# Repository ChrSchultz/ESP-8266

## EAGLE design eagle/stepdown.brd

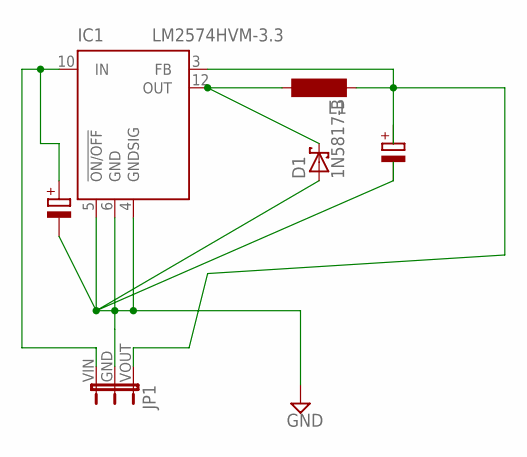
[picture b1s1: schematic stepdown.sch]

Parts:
D1: 1N5817-B; DO41-7.6
IC1: LM2574HVM-3.3; SO14W
JP1: JP2W
L1: SM-1206

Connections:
GND: D1.A, IC1.4 (GNDSIG), IC1.5 (!ON/OFF), IC1.6 (GND), JP1.GND (2)
unnamed: D1.C, IC1.12 (OUT), L1.2
unnamed: IC1.10 (IN), JP1.VIN (3)
unnamed: IC1.3 (FB), JP1.VOUT (1), L1.1

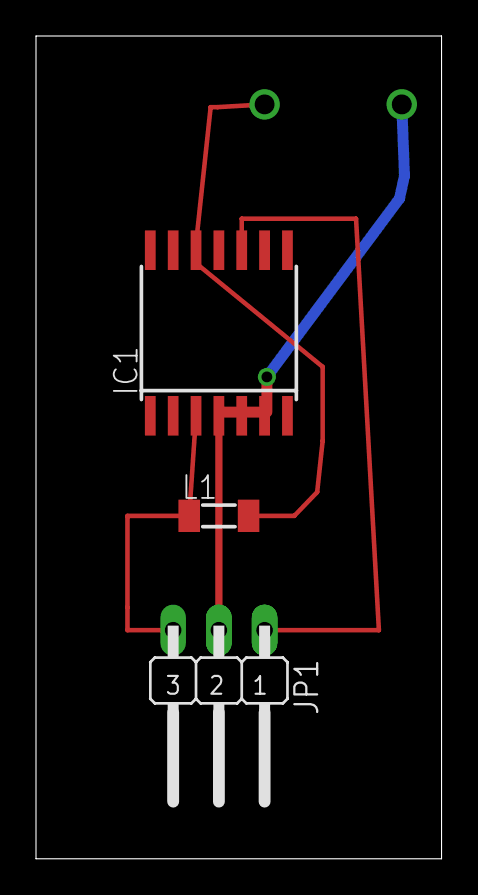
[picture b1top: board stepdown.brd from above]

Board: 2 copper layers, 22.5 x 45.7 mm, 4 parts (1 on the bottom side), 4 nets.

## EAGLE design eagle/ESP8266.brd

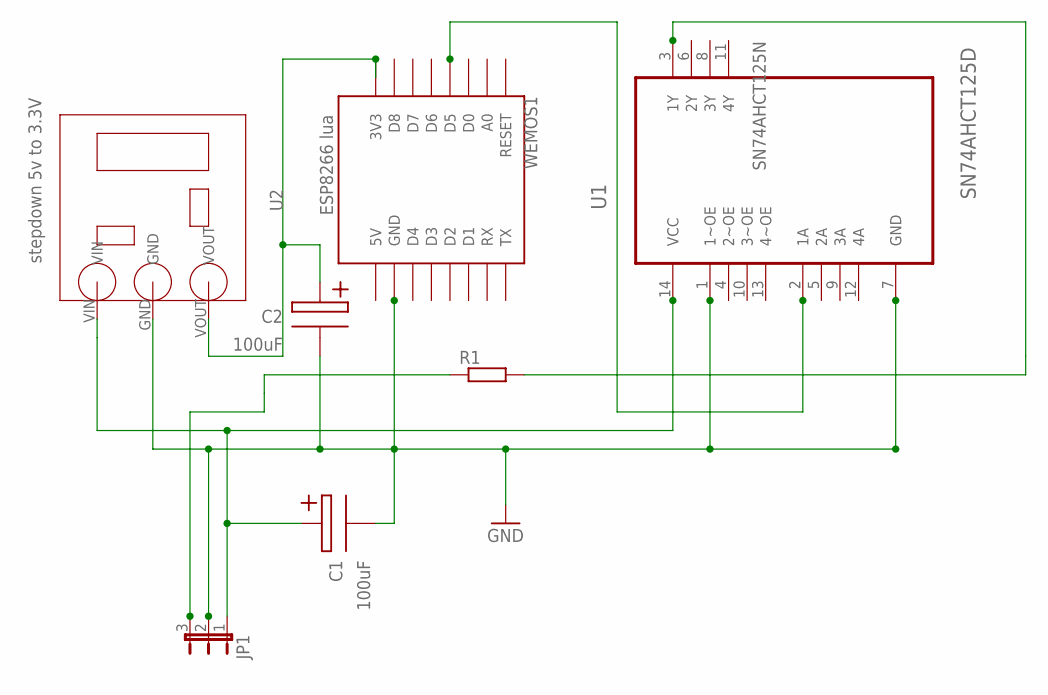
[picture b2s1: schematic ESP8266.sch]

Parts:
C1, C2: 100uF; GEPOLTER_ELEKTROLYTKONDENSATOR
JP1: JP2W
R1: R0204/7; 0204/7
U1: SN74AHCT125D; SOIC127P600X175-14N; MPN SN74AHCT125N
U2: stepdown 5v to 3.3V; STEPDOWN
WEMOS1: ESP8266 lua; WEMOS-D1-MINI

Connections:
5V: C1.+, JP1.1, U1.14 (VCC), U2.VIN
DIN: U1.2 (1A), WEMOS1.D5
DOUT: R1.2, U1.3 (1Y)
GND: C1.-, C2.-, JP1.2, U1.1 (1~OE), U1.7 (GND), U2.GND, WEMOS1.GND
SIGOUT(5V): JP1.3, R1.1
VOUT: C2.+, U2.VOUT, WEMOS1.3V3

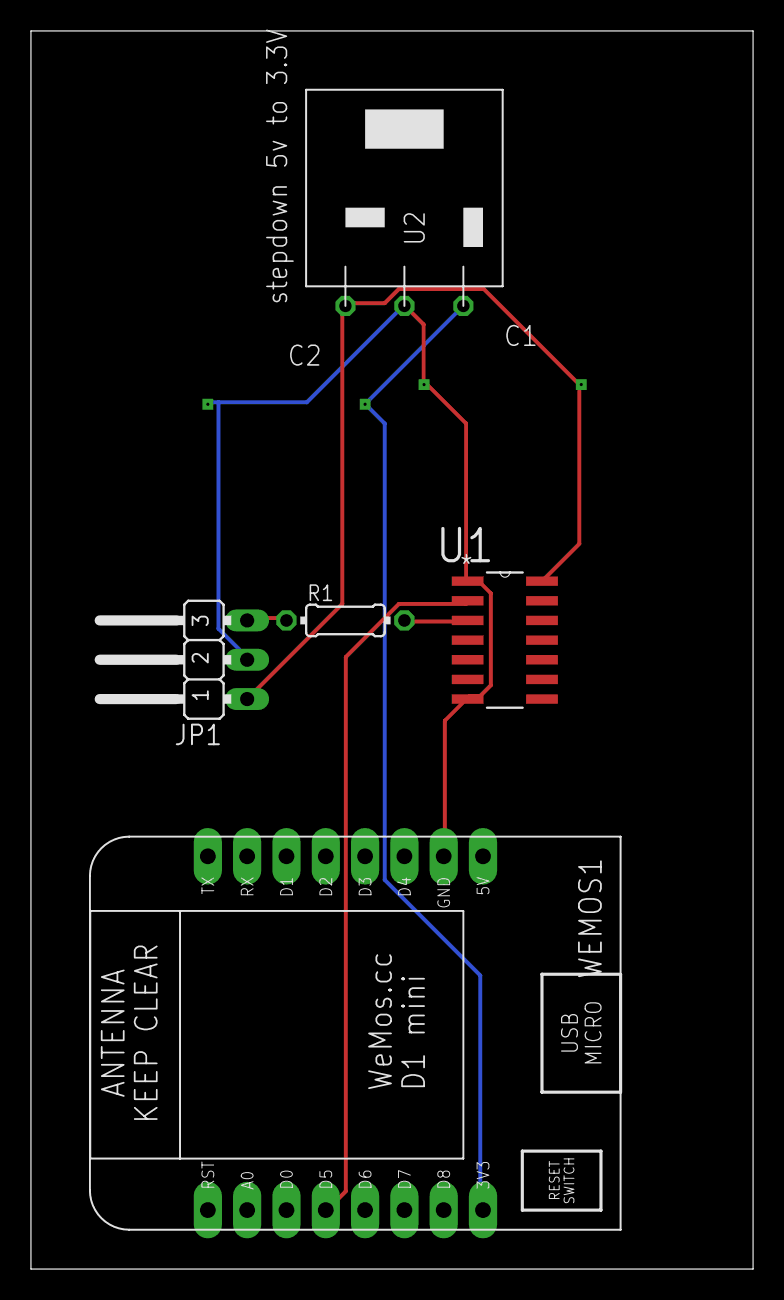
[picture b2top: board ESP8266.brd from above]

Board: 2 copper layers, 46.7 x 80.0 mm, 7 parts (0 on the bottom side), 6 nets.

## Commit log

2016-12-25 First File
2016-12-27 Teile-Dateien hinzugefügt und neue Platinenversion
2016-12-31 Eagle7 files
2016-12-31 board image added
2016-12-31 eagle deleted in master
2016-12-31 changed filenames
2016-12-31 filnames corrected
2017-01-01 stepdown controller added
2017-01-01 board updated
2017-01-01 schema updated too
2017-01-02 great fileupdate
2017-01-02 files corrected
2017-01-02 Revert "Merge remote-tracking branch 'refs/remotes/origin/master' into eagle"
    This reverts commit a46c496ff3c0c7d444fda661d166c8ecb4fd6a35, reversing
    changes made to c9c53da26b8be22d22e2eddb120c29fd7881d8ef.
2017-01-02 Revert "Revert "Merge remote-tracking branch 'refs/remotes/origin/master' into eagle""
    This reverts commit e0c2402b31a1e41b253c19088e244419ec1f6dc7.
2017-01-02 old board picture rem.
